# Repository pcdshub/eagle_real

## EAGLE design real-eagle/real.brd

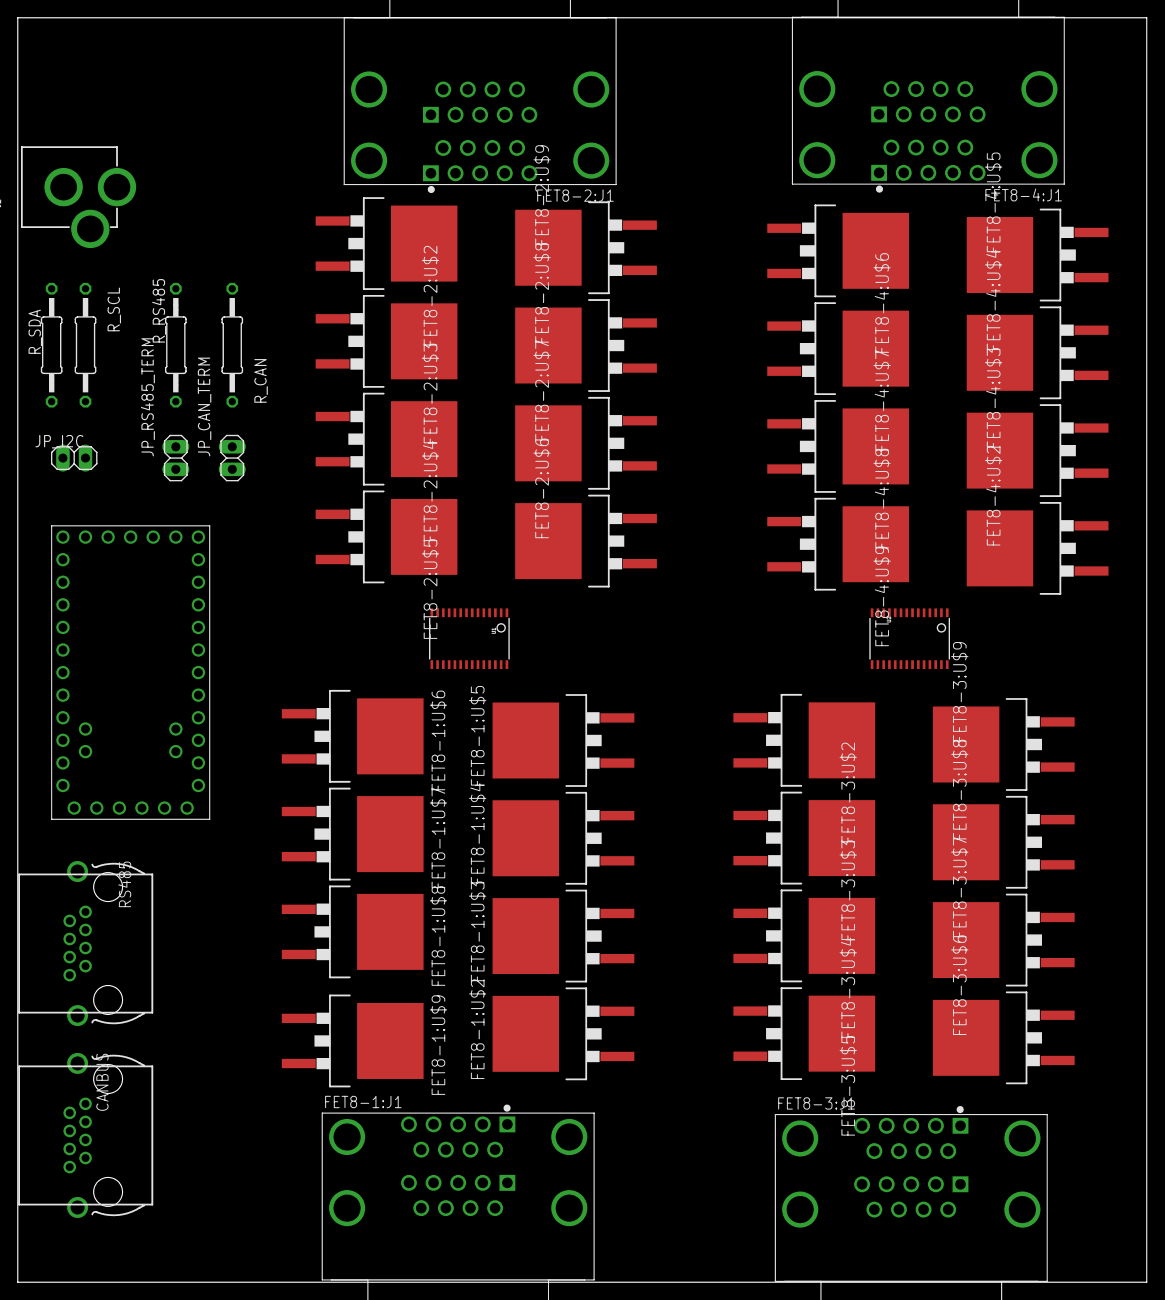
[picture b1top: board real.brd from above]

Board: 2 copper layers, 127.0 x 142.2 mm, 49 parts (0 on the bottom side), 75 nets, no tracks yet.

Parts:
CANBUS: RJ45-0446200002; 0446200002
FET8-1:J1, FET8-2:J1, FET8-3:J1, FET8-4:J1: NORCOMP_189-009-513R571
FET8-1:U$2, FET8-1:U$3, FET8-1:U$4, FET8-1:U$5, FET8-1:U$6, FET8-1:U$7, FET8-1:U$8, FET8-1:U$9, FET8-2:U$2, FET8-2:U$3, FET8-2:U$4, FET8-2:U$5, FET8-2:U$6, FET8-2:U$7, FET8-2:U$8, FET8-2:U$9, FET8-3:U$2, FET8-3:U$3, FET8-3:U$4, FET8-3:U$5, FET8-3:U$6, FET8-3:U$7, FET8-3:U$8, FET8-3:U$9, FET8-4:U$2, FET8-4:U$3, FET8-4:U$4, FET8-4:U$5, FET8-4:U$6, FET8-4:U$7, FET8-4:U$8, FET8-4:U$9: NEXFET_CSD18542KTT; D2PAK-KTT
J2: POWER_JACK; POWER_JACK_PTH
JP_CAN_TERM: 1X02
JP_I2C: 1X02
JP_RS485_TERM: 1X02
RS485: RJ45-0446200002; 0446200002
R_CAN: 120; 0207/12
R_RS485: 120; 0207/12
R_SCL: 4.7K; 0207/12
R_SDA: 4.7K; 0207/12
U1, U2: TSSOP28
U$1: CAN485FULL_SOCKET; CAN485

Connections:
ENABLE: U1.23, U2.23, U$1.A0
GND: CANBUS.3, CANBUS.6, FET8-1:J1.A9, FET8-1:J1.B9, FET8-1:J1.SH1, FET8-1:J1.SH2, FET8-1:J1.SH3, FET8-1:J1.SH4, FET8-1:U$2.3, FET8-1:U$3.3, FET8-1:U$4.3, FET8-1:U$5.3, FET8-1:U$6.3, FET8-1:U$7.3, FET8-1:U$8.3, FET8-1:U$9.3, FET8-2:J1.A9, FET8-2:J1.B9, FET8-2:J1.SH1, FET8-2:J1.SH2, FET8-2:J1.SH3, FET8-2:J1.SH4, FET8-2:U$2.3, FET8-2:U$3.3, FET8-2:U$4.3, FET8-2:U$5.3, FET8-2:U$6.3, FET8-2:U$7.3, FET8-2:U$8.3, FET8-2:U$9.3, FET8-3:J1.A9, FET8-3:J1.B9, FET8-3:J1.SH1, FET8-3:J1.SH2, FET8-3:J1.SH3, FET8-3:J1.SH4, FET8-3:U$2.3, FET8-3:U$3.3, FET8-3:U$4.3, FET8-3:U$5.3, FET8-3:U$6.3, FET8-3:U$7.3, FET8-3:U$8.3, FET8-3:U$9.3, FET8-4:J1.A9, FET8-4:J1.B9, FET8-4:J1.SH1, FET8-4:J1.SH2, FET8-4:J1.SH3, FET8-4:J1.SH4, FET8-4:U$2.3, FET8-4:U$3.3, FET8-4:U$4.3, FET8-4:U$5.3, FET8-4:U$6.3, FET8-4:U$7.3, FET8-4:U$8.3, FET8-4:U$9.3, J2.GND, J2.GNDBREAK, RS485.5, U1.2, U1.3, U1.4, U1.5, U1.14, U1.24, U1.25, U2.1, U2.3, U2.4, U2.5, U2.14, U2.24, U2.25, U$1.GND2
HEATER_A0: FET8-1:J1.A8, FET8-1:J1.B8, FET8-1:U$2.2
HEATER_A1: FET8-1:J1.A7, FET8-1:J1.B7, FET8-1:U$3.2
HEATER_A2: FET8-1:J1.A6, FET8-1:J1.B6, FET8-1:U$4.2
HEATER_A3: FET8-1:J1.A5, FET8-1:J1.B5, FET8-1:U$5.2
HEATER_A4: FET8-1:J1.A4, FET8-1:J1.B4, FET8-1:U$6.2
HEATER_A5: FET8-1:J1.A3, FET8-1:J1.B3, FET8-1:U$7.2
HEATER_A6: FET8-1:J1.A2, FET8-1:J1.B2, FET8-1:U$8.2
HEATER_A7: FET8-1:J1.A1, FET8-1:J1.B1, FET8-1:U$9.2
HEATER_B0: FET8-2:J1.A8, FET8-2:J1.B8, FET8-2:U$2.2
HEATER_B1: FET8-2:J1.A7, FET8-2:J1.B7, FET8-2:U$3.2
HEATER_B2: FET8-2:J1.A6, FET8-2:J1.B6, FET8-2:U$4.2
HEATER_B3: FET8-2:J1.A5, FET8-2:J1.B5, FET8-2:U$5.2
HEATER_B4: FET8-2:J1.A4, FET8-2:J1.B4, FET8-2:U$6.2
HEATER_B5: FET8-2:J1.A3, FET8-2:J1.B3, FET8-2:U$7.2
HEATER_B6: FET8-2:J1.A2, FET8-2:J1.B2, FET8-2:U$8.2
HEATER_B7: FET8-2:J1.A1, FET8-2:J1.B1, FET8-2:U$9.2
HEATER_C0: FET8-3:J1.A8, FET8-3:J1.B8, FET8-3:U$2.2
HEATER_C1: FET8-3:J1.A7, FET8-3:J1.B7, FET8-3:U$3.2
HEATER_C2: FET8-3:J1.A6, FET8-3:J1.B6, FET8-3:U$4.2
HEATER_C3: FET8-3:J1.A5, FET8-3:J1.B5, FET8-3:U$5.2
HEATER_C4: FET8-3:J1.A4, FET8-3:J1.B4, FET8-3:U$6.2
HEATER_C5: FET8-3:J1.A3, FET8-3:J1.B3, FET8-3:U$7.2
HEATER_C6: FET8-3:J1.A2, FET8-3:J1.B2, FET8-3:U$8.2
HEATER_C7: FET8-3:J1.A1, FET8-3:J1.B1, FET8-3:U$9.2
HEATER_D0: FET8-4:J1.A8, FET8-4:J1.B8, FET8-4:U$2.2
HEATER_D1: FET8-4:J1.A7, FET8-4:J1.B7, FET8-4:U$3.2
HEATER_D2: FET8-4:J1.A6, FET8-4:J1.B6, FET8-4:U$4.2
HEATER_D3: FET8-4:J1.A5, FET8-4:J1.B5, FET8-4:U$5.2
HEATER_D4: FET8-4:J1.A4, FET8-4:J1.B4, FET8-4:U$6.2
HEATER_D5: FET8-4:J1.A3, FET8-4:J1.B3, FET8-4:U$7.2
HEATER_D6: FET8-4:J1.A2, FET8-4:J1.B2, FET8-4:U$8.2
HEATER_D7: FET8-4:J1.A1, FET8-4:J1.B1, FET8-4:U$9.2
unnamed: JP_CAN_TERM.2, R_CAN.2
unnamed: CANBUS.7, JP_CAN_TERM.1, U$1.CANHI
unnamed: CANBUS.2, R_CAN.1, U$1.CANLO
unnamed: RS485.4, R_RS485.1, U$1.485A
unnamed: JP_RS485_TERM.2, R_RS485.2
unnamed: JP_RS485_TERM.1, RS485.3, U$1.485B
unnamed: JP_I2C.2, R_SCL.1, U1.26, U2.26, U$1.2
unnamed: JP_I2C.1, R_SDA.1, U1.27, U2.27, U$1.3
PWM_A0: FET8-1:U$2.1, U1.6
PWM_A1: FET8-1:U$3.1, U1.7
PWM_A2: FET8-1:U$4.1, U1.8
PWM_A3: FET8-1:U$5.1, U1.9
PWM_A4: FET8-1:U$6.1, U1.10
PWM_A5: FET8-1:U$7.1, U1.11
PWM_A6: FET8-1:U$8.1, U1.12
PWM_A7: FET8-1:U$9.1, U1.13
PWM_B0: FET8-2:U$2.1, U1.15
PWM_B1: FET8-2:U$3.1, U1.16
PWM_B2: FET8-2:U$4.1, U1.17
PWM_B3: FET8-2:U$5.1, U1.18
PWM_B4: FET8-2:U$6.1, U1.19
PWM_B5: FET8-2:U$7.1, U1.20
PWM_B6: FET8-2:U$8.1, U1.21
PWM_B7: FET8-2:U$9.1, U1.22
PWM_C0: FET8-3:U$2.1, U2.6
PWM_C1: FET8-3:U$3.1, U2.7
PWM_C2: FET8-3:U$4.1, U2.8
PWM_C3: FET8-3:U$5.1, U2.9
PWM_C4: FET8-3:U$6.1, U2.10
PWM_C5: FET8-3:U$7.1, U2.11
PWM_C6: FET8-3:U$8.1, U2.12
PWM_C7: FET8-3:U$9.1, U2.13
PWM_D0: FET8-4:U$2.1, U2.15
PWM_D1: FET8-4:U$3.1, U2.16
PWM_D2: FET8-4:U$4.1, U2.17
PWM_D3: FET8-4:U$5.1, U2.18
PWM_D4: FET8-4:U$6.1, U2.19
PWM_D5: FET8-4:U$7.1, U2.20
PWM_D6: FET8-4:U$8.1, U2.21
PWM_D7: FET8-4:U$9.1, U2.22
VCC: J2.PWR, R_SCL.2, R_SDA.2, U1.1, U1.28, U2.2, U2.28, U$1.VCC

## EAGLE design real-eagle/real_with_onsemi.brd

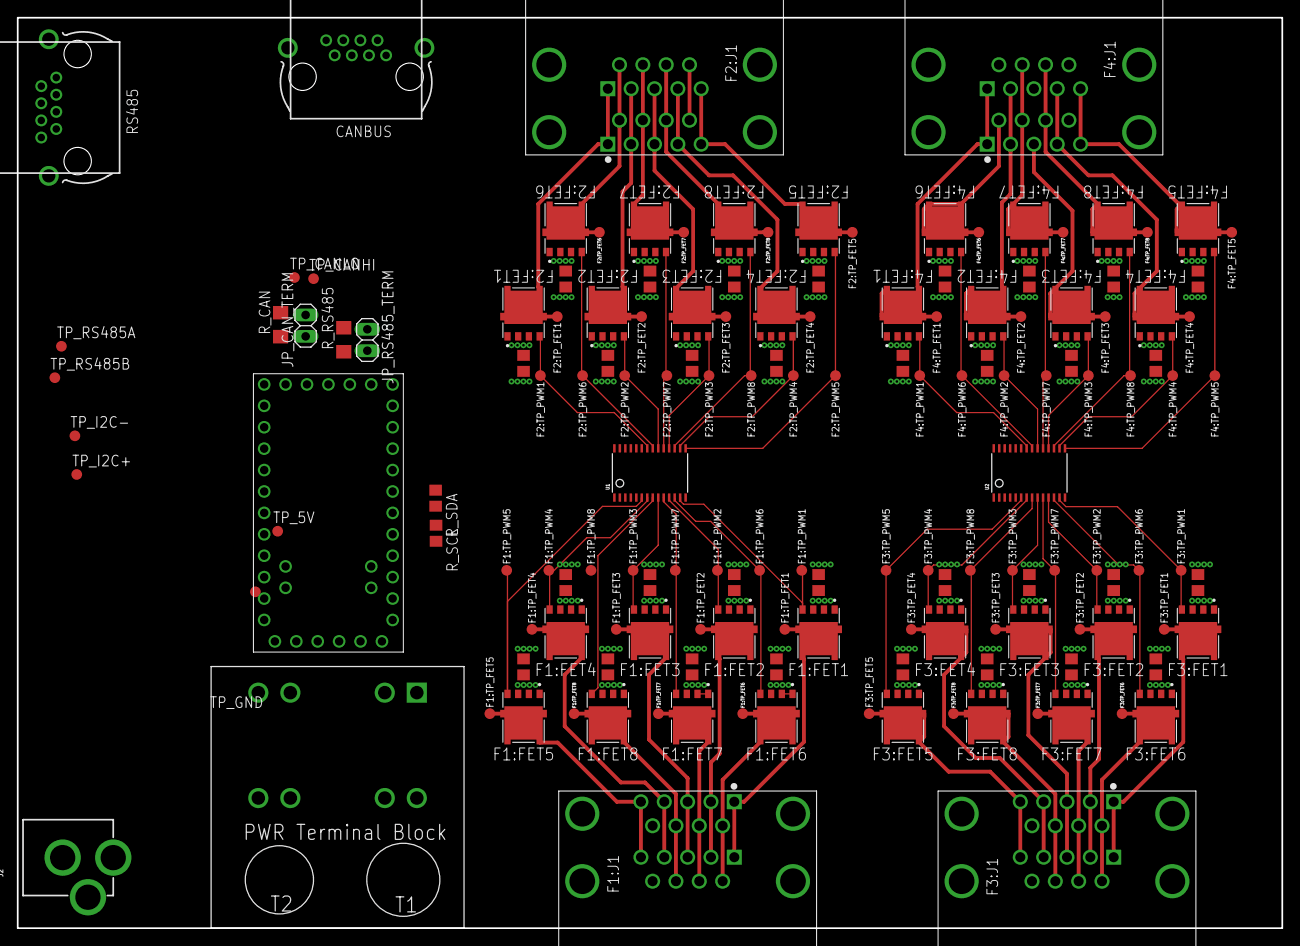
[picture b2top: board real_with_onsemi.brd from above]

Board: 4 copper layers, 150.0 x 108.0 mm, 153 parts (0 on the bottom side), 76 nets.

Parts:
CANBUS: RJ45-0446200002; 0446200002
F1:C1, F1:C2, F1:C3, F1:C4, F1:C5, F1:C6, F1:C7, F1:C8, F2:C1, F2:C2, F2:C3, F2:C4, F2:C5, F2:C6, F2:C7, F2:C8, F3:C1, F3:C2, F3:C3, F3:C4, F3:C5, F3:C6, F3:C7, F3:C8, F4:C1, F4:C2, F4:C3, F4:C4, F4:C5, F4:C6, F4:C7, F4:C8: C0805
F1:FET1, F1:FET2, F1:FET3, F1:FET4, F1:FET5, F1:FET6, F1:FET7, F1:FET8, F2:FET1, F2:FET2, F2:FET3, F2:FET4, F2:FET5, F2:FET6, F2:FET7, F2:FET8, F3:FET1, F3:FET2, F3:FET3, F3:FET4, F3:FET5, F3:FET6, F3:FET7, F3:FET8, F4:FET1, F4:FET2, F4:FET3, F4:FET4, F4:FET5, F4:FET6, F4:FET7, F4:FET8: ONSEMI_FET_NVMFS5C604NL; DFN500X600X110-5N
F1:J1, F2:J1, F3:J1, F4:J1: NORCOMP_189-009-513R571
F1:TP_FET1, F1:TP_FET2, F1:TP_FET3, F1:TP_FET4, F1:TP_FET5, F1:TP_FET6, F1:TP_FET7, F1:TP_FET8, F1:TP_PWM1, F1:TP_PWM2, F1:TP_PWM3, F1:TP_PWM4, F1:TP_PWM5, F1:TP_PWM6, F1:TP_PWM7, F1:TP_PWM8, F2:TP_FET1, F2:TP_FET2, F2:TP_FET3, F2:TP_FET4, F2:TP_FET5, F2:TP_FET6, F2:TP_FET7, F2:TP_FET8, F2:TP_PWM1, F2:TP_PWM2, F2:TP_PWM3, F2:TP_PWM4, F2:TP_PWM5, F2:TP_PWM6, F2:TP_PWM7, F2:TP_PWM8, F3:TP_FET1, F3:TP_FET2, F3:TP_FET3, F3:TP_FET4, F3:TP_FET5, F3:TP_FET6, F3:TP_FET7, F3:TP_FET8, F3:TP_PWM1, F3:TP_PWM2, F3:TP_PWM3, F3:TP_PWM4, F3:TP_PWM5, F3:TP_PWM6, F3:TP_PWM7, F3:TP_PWM8, F4:TP_FET1, F4:TP_FET2, F4:TP_FET3, F4:TP_FET4, F4:TP_FET5, F4:TP_FET6, F4:TP_FET7, F4:TP_FET8, F4:TP_PWM1, F4:TP_PWM2, F4:TP_PWM3, F4:TP_PWM4, F4:TP_PWM5, F4:TP_PWM6, F4:TP_PWM7, F4:TP_PWM8: TPB1,27; B1,27
J2: POWER_JACK; POWER_JACK_PTH
JP_CAN_TERM: 1X02
JP_RS485_TERM: 1X02
J_48V: PHOENIX_TERMINAL_BLOCK; TERMINAL_BLOCK_PHOENIX
RS485: RJ45-0446200002; 0446200002
R_CAN: 120; R1206
R_RS485: 120; R1206
R_SCL: 4.7k; R0805
R_SDA: 4.7k; R0805
TP_5V: TPB1,27; B1,27
TP_CANHI: TPB1,27; B1,27
TP_CANLO: TPB1,27; B1,27
TP_GND: TPB1,27; B1,27
TP_I2C+, TP_I2C-: TPB1,27; B1,27
TP_RS485A, TP_RS485B: TPB1,27; B1,27
U1, U2: TSSOP28
U$1: CAN485FULL_SOCKET; CAN485

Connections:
ENABLE: U1.23, U2.23, U$1.A0
GND: CANBUS.3, CANBUS.6, F1:C1.2, F1:C2.2, F1:C3.2, F1:C4.2, F1:C5.2, F1:C6.2, F1:C7.2, F1:C8.2, F1:FET1.1, F1:FET1.2, F1:FET1.3, F1:FET2.1, F1:FET2.2, F1:FET2.3, F1:FET3.1, F1:FET3.2, F1:FET3.3, F1:FET4.1, F1:FET4.2, F1:FET4.3, F1:FET5.1, F1:FET5.2, F1:FET5.3, F1:FET6.1, F1:FET6.2, F1:FET6.3, F1:FET7.1, F1:FET7.2, F1:FET7.3, F1:FET8.1, F1:FET8.2, F1:FET8.3, F1:J1.A9, F1:J1.B9, F1:J1.SH1, F1:J1.SH2, F1:J1.SH3, F1:J1.SH4, F2:C1.2, F2:C2.2, F2:C3.2, F2:C4.2, F2:C5.2, F2:C6.2, F2:C7.2, F2:C8.2, F2:FET1.1, F2:FET1.2, F2:FET1.3, F2:FET2.1, F2:FET2.2, F2:FET2.3, F2:FET3.1, F2:FET3.2, F2:FET3.3, F2:FET4.1, F2:FET4.2, F2:FET4.3, F2:FET5.1, F2:FET5.2, F2:FET5.3, F2:FET6.1, F2:FET6.2, F2:FET6.3, F2:FET7.1, F2:FET7.2, F2:FET7.3, F2:FET8.1, F2:FET8.2, F2:FET8.3, F2:J1.A9, F2:J1.B9, F2:J1.SH1, F2:J1.SH2, F2:J1.SH3, F2:J1.SH4, F3:C1.2, F3:C2.2, F3:C3.2, F3:C4.2, F3:C5.2, F3:C6.2, F3:C7.2, F3:C8.2, F3:FET1.1, F3:FET1.2, F3:FET1.3, F3:FET2.1, F3:FET2.2, F3:FET2.3, F3:FET3.1, F3:FET3.2, F3:FET3.3, F3:FET4.1, F3:FET4.2, F3:FET4.3, F3:FET5.1, F3:FET5.2, F3:FET5.3, F3:FET6.1, F3:FET6.2, F3:FET6.3, F3:FET7.1, F3:FET7.2, F3:FET7.3, F3:FET8.1, F3:FET8.2, F3:FET8.3, F3:J1.A9, F3:J1.B9, F3:J1.SH1, F3:J1.SH2, F3:J1.SH3, F3:J1.SH4, F4:C1.2, F4:C2.2, F4:C3.2, F4:C4.2, F4:C5.2, F4:C6.2, F4:C7.2, F4:C8.2, F4:FET1.1, F4:FET1.2, F4:FET1.3, F4:FET2.1, F4:FET2.2, F4:FET2.3, F4:FET3.1, F4:FET3.2, F4:FET3.3, F4:FET4.1, F4:FET4.2, F4:FET4.3, F4:FET5.1, F4:FET5.2, F4:FET5.3, F4:FET6.1, F4:FET6.2, F4:FET6.3, F4:FET7.1, F4:FET7.2, F4:FET7.3, F4:FET8.1, F4:FET8.2, F4:FET8.3, F4:J1.A9, F4:J1.B9, F4:J1.SH1, F4:J1.SH2, F4:J1.SH3, F4:J1.SH4, J2.GND, J2.GNDBREAK, J_48V.P$3, J_48V.P$4, J_48V.P$7, J_48V.P$8, RS485.5, TP_GND.TP, U1.2, U1.3, U1.4, U1.5, U1.14, U1.24, U1.25, U2.1, U2.3, U2.4, U2.5, U2.14, U2.24, U2.25, U$1.GND2
HEATER_A0: F1:FET1.5@1, F1:FET1.5@2, F1:FET1.5@3, F1:FET1.5@4, F1:FET1.5@5, F1:J1.A1, F1:J1.B1, F1:TP_FET1.TP
HEATER_A1: F1:FET2.5@1, F1:FET2.5@2, F1:FET2.5@3, F1:FET2.5@4, F1:FET2.5@5, F1:J1.A2, F1:J1.B2, F1:TP_FET2.TP
HEATER_A2: F1:FET3.5@1, F1:FET3.5@2, F1:FET3.5@3, F1:FET3.5@4, F1:FET3.5@5, F1:J1.A3, F1:J1.B3, F1:TP_FET3.TP
HEATER_A3: F1:FET4.5@1, F1:FET4.5@2, F1:FET4.5@3, F1:FET4.5@4, F1:FET4.5@5, F1:J1.A4, F1:J1.B4, F1:TP_FET4.TP
HEATER_A4: F1:FET5.5@1, F1:FET5.5@2, F1:FET5.5@3, F1:FET5.5@4, F1:FET5.5@5, F1:J1.A5, F1:J1.B5, F1:TP_FET5.TP
HEATER_A5: F1:FET6.5@1, F1:FET6.5@2, F1:FET6.5@3, F1:FET6.5@4, F1:FET6.5@5, F1:J1.A6, F1:J1.B6, F1:TP_FET6.TP
HEATER_A6: F1:FET7.5@1, F1:FET7.5@2, F1:FET7.5@3, F1:FET7.5@4, F1:FET7.5@5, F1:J1.A7, F1:J1.B7, F1:TP_FET7.TP
HEATER_A7: F1:FET8.5@1, F1:FET8.5@2, F1:FET8.5@3, F1:FET8.5@4, F1:FET8.5@5, F1:J1.A8, F1:J1.B8, F1:TP_FET8.TP
HEATER_B0: F2:FET1.5@1, F2:FET1.5@2, F2:FET1.5@3, F2:FET1.5@4, F2:FET1.5@5, F2:J1.A1, F2:J1.B1, F2:TP_FET1.TP
HEATER_B1: F2:FET2.5@1, F2:FET2.5@2, F2:FET2.5@3, F2:FET2.5@4, F2:FET2.5@5, F2:J1.A2, F2:J1.B2, F2:TP_FET2.TP
HEATER_B2: F2:FET3.5@1, F2:FET3.5@2, F2:FET3.5@3, F2:FET3.5@4, F2:FET3.5@5, F2:J1.A3, F2:J1.B3, F2:TP_FET3.TP
HEATER_B3: F2:FET4.5@1, F2:FET4.5@2, F2:FET4.5@3, F2:FET4.5@4, F2:FET4.5@5, F2:J1.A4, F2:J1.B4, F2:TP_FET4.TP
HEATER_B4: F2:FET5.5@1, F2:FET5.5@2, F2:FET5.5@3, F2:FET5.5@4, F2:FET5.5@5, F2:J1.A5, F2:J1.B5, F2:TP_FET5.TP
HEATER_B5: F2:FET6.5@1, F2:FET6.5@2, F2:FET6.5@3, F2:FET6.5@4, F2:FET6.5@5, F2:J1.A6, F2:J1.B6, F2:TP_FET6.TP
HEATER_B6: F2:FET7.5@1, F2:FET7.5@2, F2:FET7.5@3, F2:FET7.5@4, F2:FET7.5@5, F2:J1.A7, F2:J1.B7, F2:TP_FET7.TP
HEATER_B7: F2:FET8.5@1, F2:FET8.5@2, F2:FET8.5@3, F2:FET8.5@4, F2:FET8.5@5, F2:J1.A8, F2:J1.B8, F2:TP_FET8.TP
HEATER_C0: F3:FET1.5@1, F3:FET1.5@2, F3:FET1.5@3, F3:FET1.5@4, F3:FET1.5@5, F3:J1.A1, F3:J1.B1, F3:TP_FET1.TP
HEATER_C1: F3:FET2.5@1, F3:FET2.5@2, F3:FET2.5@3, F3:FET2.5@4, F3:FET2.5@5, F3:J1.A2, F3:J1.B2, F3:TP_FET2.TP
HEATER_C2: F3:FET3.5@1, F3:FET3.5@2, F3:FET3.5@3, F3:FET3.5@4, F3:FET3.5@5, F3:J1.A3, F3:J1.B3, F3:TP_FET3.TP
HEATER_C3: F3:FET4.5@1, F3:FET4.5@2, F3:FET4.5@3, F3:FET4.5@4, F3:FET4.5@5, F3:J1.A4, F3:J1.B4, F3:TP_FET4.TP
HEATER_C4: F3:FET5.5@1, F3:FET5.5@2, F3:FET5.5@3, F3:FET5.5@4, F3:FET5.5@5, F3:J1.A5, F3:J1.B5, F3:TP_FET5.TP
HEATER_C5: F3:FET6.5@1, F3:FET6.5@2, F3:FET6.5@3, F3:FET6.5@4, F3:FET6.5@5, F3:J1.A6, F3:J1.B6, F3:TP_FET6.TP
HEATER_C6: F3:FET7.5@1, F3:FET7.5@2, F3:FET7.5@3, F3:FET7.5@4, F3:FET7.5@5, F3:J1.A7, F3:J1.B7, F3:TP_FET7.TP
HEATER_C7: F3:FET8.5@1, F3:FET8.5@2, F3:FET8.5@3, F3:FET8.5@4, F3:FET8.5@5, F3:J1.A8, F3:J1.B8, F3:TP_FET8.TP
HEATER_D0: F4:FET1.5@1, F4:FET1.5@2, F4:FET1.5@3, F4:FET1.5@4, F4:FET1.5@5, F4:J1.A1, F4:J1.B1, F4:TP_FET1.TP
HEATER_D1: F4:FET2.5@1, F4:FET2.5@2, F4:FET2.5@3, F4:FET2.5@4, F4:FET2.5@5, F4:J1.A2, F4:J1.B2, F4:TP_FET2.TP
HEATER_D2: F4:FET3.5@1, F4:FET3.5@2, F4:FET3.5@3, F4:FET3.5@4, F4:FET3.5@5, F4:J1.A3, F4:J1.B3, F4:TP_FET3.TP
HEATER_D3: F4:FET4.5@1, F4:FET4.5@2, F4:FET4.5@3, F4:FET4.5@4, F4:FET4.5@5, F4:J1.A4, F4:J1.B4, F4:TP_FET4.TP
HEATER_D4: F4:FET5.5@1, F4:FET5.5@2, F4:FET5.5@3, F4:FET5.5@4, F4:FET5.5@5, F4:J1.A5, F4:J1.B5, F4:TP_FET5.TP
HEATER_D5: F4:FET6.5@1, F4:FET6.5@2, F4:FET6.5@3, F4:FET6.5@4, F4:FET6.5@5, F4:J1.A6, F4:J1.B6, F4:TP_FET6.TP
HEATER_D6: F4:FET7.5@1, F4:FET7.5@2, F4:FET7.5@3, F4:FET7.5@4, F4:FET7.5@5, F4:J1.A7, F4:J1.B7, F4:TP_FET7.TP
HEATER_D7: F4:FET8.5@1, F4:FET8.5@2, F4:FET8.5@3, F4:FET8.5@4, F4:FET8.5@5, F4:J1.A8, F4:J1.B8, F4:TP_FET8.TP
unnamed: JP_CAN_TERM.2, R_CAN.1, TP_CANLO.TP
unnamed: CANBUS.7, JP_CAN_TERM.1, TP_CANHI.TP, U$1.CANHI
unnamed: CANBUS.2, R_CAN.2, U$1.CANLO
unnamed: RS485.4, R_RS485.1, U$1.485A
unnamed: JP_RS485_TERM.2, R_RS485.2
unnamed: JP_RS485_TERM.1, RS485.3, U$1.485B
unnamed: R_SCL.1, U1.26, U2.26, U$1.2
unnamed: R_SDA.1, U1.27, U2.27, U$1.3
PWM_A0: F1:FET5.4, F1:TP_PWM5.TP, U1.6
PWM_A1: F1:FET4.4, F1:TP_PWM4.TP, U1.7
PWM_A2: F1:FET8.4, F1:TP_PWM8.TP, U1.8
PWM_A3: F1:FET3.4, F1:TP_PWM3.TP, U1.9
PWM_A4: F1:FET7.4, F1:TP_PWM7.TP, U1.10
PWM_A5: F1:FET2.4, F1:TP_PWM2.TP, U1.11
PWM_A6: F1:FET6.4, F1:TP_PWM6.TP, U1.12
PWM_A7: F1:FET1.4, F1:TP_PWM1.TP, U1.13
PWM_B0: F2:FET5.4, F2:TP_PWM5.TP, U1.15
PWM_B1: F2:FET4.4, F2:TP_PWM4.TP, U1.16
PWM_B2: F2:FET8.4, F2:TP_PWM8.TP, U1.17
PWM_B3: F2:FET3.4, F2:TP_PWM3.TP, U1.18
PWM_B4: F2:FET7.4, F2:TP_PWM7.TP, U1.19
PWM_B5: F2:FET2.4, F2:TP_PWM2.TP, U1.20
PWM_B6: F2:FET6.4, F2:TP_PWM6.TP, U1.21
PWM_B7: F2:FET1.4, F2:TP_PWM1.TP, U1.22
PWM_C0: F3:FET5.4, F3:TP_PWM5.TP, U2.6
PWM_C1: F3:FET4.4, F3:TP_PWM4.TP, U2.7
PWM_C2: F3:FET8.4, F3:TP_PWM8.TP, U2.8
PWM_C3: F3:FET3.4, F3:TP_PWM3.TP, U2.9
PWM_C4: F3:FET7.4, F3:TP_PWM7.TP, U2.10
PWM_C5: F3:FET2.4, F3:TP_PWM2.TP, U2.11
PWM_C6: F3:FET6.4, F3:TP_PWM6.TP, U2.12
PWM_C7: F3:FET1.4, F3:TP_PWM1.TP, U2.13
PWM_D0: F4:FET5.4, F4:TP_PWM5.TP, U2.15
PWM_D1: F4:FET4.4, F4:TP_PWM4.TP, U2.16
PWM_D2: F4:FET8.4, F4:TP_PWM8.TP, U2.17
PWM_D3: F4:FET3.4, F4:TP_PWM3.TP, U2.18
PWM_D4: F4:FET7.4, F4:TP_PWM7.TP, U2.19
PWM_D5: F4:FET2.4, F4:TP_PWM2.TP, U2.20
PWM_D6: F4:FET6.4, F4:TP_PWM6.TP, U2.21
PWM_D7: F4:FET1.4, F4:TP_PWM1.TP, U2.22
VCC: J2.PWR, R_SCL.2, R_SDA.2, TP_5V.TP, U1.1, U1.28, U2.2, U2.28, U$1.VCC
V_48V: F1:C1.1, F1:C2.1, F1:C3.1, F1:C4.1, F1:C5.1, F1:C6.1, F1:C7.1, F1:C8.1, F2:C1.1, F2:C2.1, F2:C3.1, F2:C4.1, F2:C5.1, F2:C6.1, F2:C7.1, F2:C8.1, F3:C1.1, F3:C2.1, F3:C3.1, F3:C4.1, F3:C5.1, F3:C6.1, F3:C7.1, F3:C8.1, F4:C1.1, F4:C2.1, F4:C3.1, F4:C4.1, F4:C5.1, F4:C6.1, F4:C7.1, F4:C8.1, J_48V.P$1, J_48V.P$2, J_48V.P$5, J_48V.P$6

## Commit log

2019-01-30 Schematic without layout
2019-01-31 onsemi NMOS version
2019-01-31 Basis for routing
    Route commands:
    auto PWM_A0 PWM_A1 PWM_A2 PWM_A3 PWM_A4 PWM_A5 PWM_A6 PWM_A7 HEATER_A0 HEATER_A1 HEATER_A2 HEATER_A3 HEATER_A4 HEATER_A5 HEATER_A6 HEATER_A7 PWM_B0 PWM_B1 PWM_B2 PWM_B3 PWM_B4 PWM_B5 PWM_B6 PWM_B7 HE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
    auto PWM_C0 PWM_C1 PWM_C2 PWM_C3 PWM_C4 PWM_C5 PWM_C6 PWM_C7 HEATER_C0 HEATER_C1 HEATER_C2 HEATER_C3 HEATER_C4 HEATER_C5 HEATER_C6 HEATER_C7 PWM_D0 PWM_D1 PWM_D2 PWM_D3 PWM_D4 PWM_D5 PWM_D6 PWM_D7 HE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
    auto ! gnd
2019-01-31 Routed except vcc/gnd
2019-01-31 Add useful tool - moving items by certain amounts
2019-02-01 Rename FET8-X->FX, move names/values for silkscreen
2019-02-01 Tweak value positions
2019-02-01 move heater -> net class 10
2019-02-27 Add modifications from @slacAdpai as of 2019/2/27
2025-04-15 MNT: Adding CODEOWNERS file
